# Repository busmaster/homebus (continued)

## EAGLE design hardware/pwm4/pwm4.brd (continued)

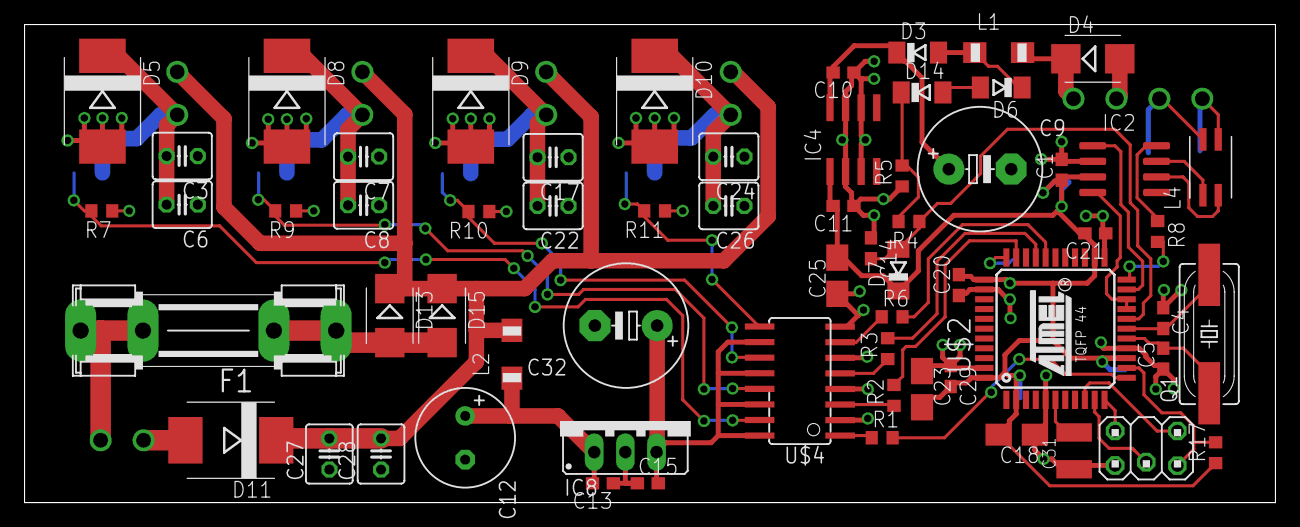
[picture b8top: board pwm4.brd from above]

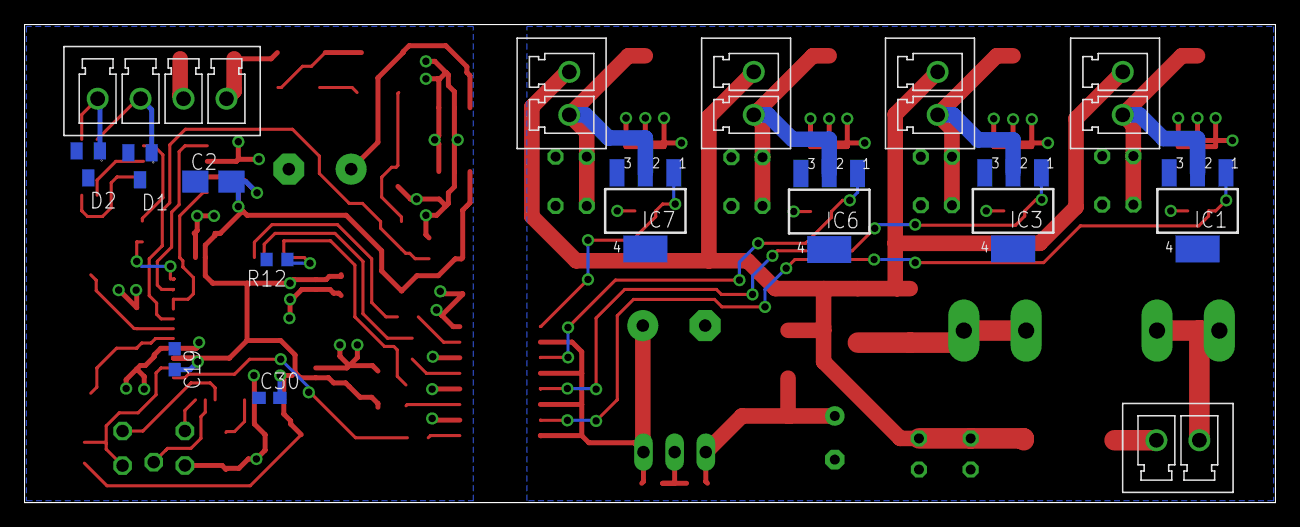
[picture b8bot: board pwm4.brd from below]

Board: 2 copper layers, 102.0 x 39.0 mm, 79 parts (16 on the bottom side), 46 nets.

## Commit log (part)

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2015-11-28 status led integration
2015-11-29 allow client pty while sio device is not yet available
2015-12-01 mega88 clock calibration
2015-12-05 correction of build directory path
2016-01-25 new bus telegram types for clock calibration
2016-01-25 clock calibration
2016-01-25 clock calibraton firmware for atmega88 based devices
2016-02-01 sio send lockup
2016-02-01 change of manufacturer and product string
2016-02-09 sio driver reports one received character on startup
2016-02-09 file mode changes
2016-02-11 Update README
    Test2
2016-02-19 elko position move
2016-02-23 bootloader for rs485if
2016-02-25 Fix usage message in eventmonitor and monitor
2016-02-29 firmwareupdate doesn't start due to buffered rx frames in sio device
2016-02-29 adapt file mode
2016-02-29 remove debug sio support
2016-02-29 prepare usage of siosingle
2016-03-08 removed bit offset undefs for m128 (moved to sio_c.h)
2016-03-08 version 1.05 (use of siosingle)
2016-03-08 use of siosingle for switchv2
2016-03-08 preparation for siosingle usage at do31 and rs485if
2016-03-13 board specific modules for rs485if
2016-03-15 atmega1284 adaptions
2016-03-19 dmx test
2016-03-19 correction of BUS_TRANSCEIVER_POWER_UP macro
2016-03-19 part value actualization
2016-03-19 set unix line termination
2016-03-20 port settings
2016-04-10 doc for initial flash setup
2016-04-10 correction of programming steps
2016-05-09 change actval from max wind to current wind
2016-05-16 auto switch off for lamp in garage and bathroom
2016-05-30 read command from stdin to terminate process
2016-05-30 correction of select rfds setup
2016-06-27 New window for kitchen. Support addition kitchen lamp.
2016-06-27 new window for kitchen
2016-09-18 change of socket_1 relais connection from NO to NC
2016-09-18 add support for 14.7456MHz and 1.8432MHz clock
2016-09-18 hardware design pwm4
2016-09-19 new command: generate a switch event
2016-09-21 set default own address in server mode
2016-09-21 set default own address in server mode to command line parameter
2016-09-21 converted to unix line termination
2016-09-21 setup window for disabling the doorbell
2016-10-01 changed crystal frequency
2016-10-01 add support for rs485if and pwm4 devices
2016-10-03 initial version of pwm4 application
2016-10-03 missing file
2016-10-03 rs485 test
2016-10-03 support for rs485f and pwm4
2016-10-10 reduce flash usage by sio tx simplification
2016-10-15 support rs485if and pwm4 actval
2016-10-15 optocoupler input and output resistor change
2016-10-17 output restore on power on
2016-10-17 unix line termination
2016-10-17 pwm for switch 46
2016-10-25 new command inforange for bus scan
2016-10-30 enable pullup on all input pins
2016-12-14 missing header
2017-01-03 save max wind value to eeprom
2017-01-03 rearrangement of buttons
2017-01-03 file mode
2017-01-04 sleep before flushing the sio input on startup
2017-01-17 use siosingle
2017-01-31 pwm4: set pwm frequency to 900 Hz from 225 Hz
    This high frequency is required due to instability of the used power supply
    (Meanwell LRS-50-24).
2017-01-31 pwm4 sio: support for additional cpu clocks
2017-02-18 eventmonitor: support device type PWM4
2017-02-27 removed debug print
2017-02-28 pwm: extension of interface: separate function for on/off
2017-02-28 sio: support EVEN parity
2017-02-28 pwm4 application: use extended pwm interface
2017-02-28 smartmeter tool: use EVEN parity
2017-02-28 new hardware: smartmeter interface
2017-03-14 smartmeterif: initial debug version
2017-03-18 smartmeter support
2017-03-18 pwm4: renaming mask -> set
2017-03-19 add new telegram type for diag data
2017-03-19 monitor: add support for diag telegram
2017-04-04 pwm4 application: delayed switch off of the common power supply
2017-04-04 smartmeterif hardware: value changes
2017-05-07 change \r\n to \n
2017-05-07 fflush stdout
2017-05-09 visu: reduce code duplication
2017-05-13 modulservice: check receiver address
2017-05-24 tools: mqtt: initial demo version
2017-06-04 mqtt: test
2017-06-04 tools: mqtt: pasre command line params
2017-06-05 tools: eventmonitor: optional listen only mode
2017-06-05 tools: mqtt: parameter for event listen address
2017-06-05 do31: eBusDevReqSetClientAddr does not work
2017-06-19 pwm4: unable to switch on after power fail
2017-06-20 tools: mqtt: subscriber support for do31 shader
2017-07-02 tools: mqtt: command line parameter for broker address/port
2017-07-02 tools: mqtt: debian init script example
2017-07-11 tools: mqtt: wait for response on DO31 ReqSetValue
2017-07-11 usbif: use siosingle
2017-07-15 tools: bottongpio: initial version
2017-07-15 tools: buttongpio: wrong telegram processing
2017-07-16 tool: mqtt: extend example configuration
2017-07-22 tools: mqtt: add lights stairs
2017-07-25 tools: modulservice: support changed pwm4 actval protocol
2017-07-25 pwm4: wrong actval state
2017-07-29 tools: mqtt: add PWM4 support
2017-08-09 tools: mqtt: sw8 device support
2017-10-17 buttongpio: trigger on swtichstate additionally
2017-10-31 switchv2a: replace switchState by actualValue telegrams
2017-10-31 project241: use eDigOut30 for door light
2017-11-07 bus: introduction gettime/settime telegram types
2017-11-11 application240: door light auto/on/off
2017-11-11 mqtt: topic extension
2017-11-12 buttongpio: add supoort for eBusDevReqActualValueEvent/sw8 telegram
2017-11-20 visu: implement ButtonBackPressed to call dialog's hide methode
2017-11-20 visu: support mjpeg camera
2017-11-26 visu: auto mode for door light
2017-11-27 visu: remove moduleservice debug prints
2017-11-28 visu: smartmeter support
2017-12-05 added .gitignore
2017-12-05 visu: do not smartmeter from startup
2017-12-11 add missing files
2017-12-11 add hardware
2018-02-24 monitor: support eBusDevTypeSmIf
2018-02-24 change to unix line ending
2018-02-25 switchv2_garage: optimize for size
2018-02-25 switchv2_luminance: optimize for size
2018-02-25 monitor: add setvar/getvar support
2018-02-25 monitor: output format cleanup
2018-04-03 bus: busvar support
2018-04-03 monitor: use variable for compiler options
2018-04-03 monitor: add setvar/getvar result code
2018-04-07 busvar: change index type to uint8_t from uint16_t
2018-04-08 monitor: wrong usage help for option logfile
2018-05-12 busvar: stabilisation
2018-06-26 busvar: make variable value peristent to eeprom optionally
2018-06-26 klaus240: use siosingle
2018-07-28 tools: initial varserver
2018-09-22 bustest: correction of library dependency order
2018-10-08 bus: pwm16 protocol support
2019-01-19 sonoff_socket: initial version
2019-10-30 sw88 1.06 hAT
2019-10-30 Anpassungen
2019-10-30 gitignore
2019-10-30 Hardwarelayouts
2019-10-30 Bootloader
2019-10-30 pwm16
2019-10-30 Projekt hinzugefügt
2019-10-30 missing makefile
2019-10-30 Eagle Files pwm16 added
2019-11-01 Portserver für Webapp
2019-11-07 spelling error
2019-11-08 tasttimeout
2019-11-25 do31: set reset state of interrupt mask registers
    The bootloader might leave interrupt mask register settings that
    can trigger unexcepted interrupts. These unexpected interrupt are
    handled by the default handler that calls the reset handler.
2020-05-03 mqtt: support sw8 input actval event
    On publishing mqtt sw8 input events a bus actval event is generated:
    mosq_publish ... -t home/eingang/bewegungsmelder/set -m 1
    -> bus actval event to all receivers from the configuration receiver option
    -> mqtt publish home/eingang/bewegungsmelder/actual
    The configuration has to be extended by the receiver option, e.g.:
    - topic: home/eingang/bewegungsmelder
2020-05-24 busvar: whitespace cleanup
2020-05-29 mqtt: add bus variable support
    bus device sends ReqSetVar to mqtt -> publish variable actual value
    publish variable set value to mqtt -> ReqSetVar to bus device
    To enable subscribtion to bus variables the bus device has to send ReqSetVar
    to mqtt virtual bus device.
2020-05-31 monitor: fix line feed output of RespSetVar
2020-05-31 visu: use new creator
2020-06-09 mqtt: publish var directly on var subscription callback
    Before publish var was triggered by bus ReqSetVar only.
2020-06-11 mqtt: do not publish retained
2020-06-11 mqtt: undo disable retained messages
2020-06-14 mqtt: support DO31 active low outputs
2020-06-14 mqtt: rename variable topic in example config
2020-06-19 visu: replace the proprietary device access with mqtt
2020-06-21 visu: remove unused variable
2020-06-23 klaus240: use bus variables for bell mode and door light mode
2020-07-03 bus: extend ActualValueEvent by smif
2020-07-03 smif: add ActualValueEvent for smartmeter data
    The ActualValueEvent is enabled by setting bus variable 0 to 1.
    After N seconds bus variable 0 is reset automatically. N is read from
    bus variable 1. The receiver address of the ActualValueEvent is read from
    bus varibale 2.
2020-07-04 smif: fix message type for ActualValueEvent
2020-07-04 monitor: add supoort for smif ActualValueEvent
2020-07-04 visu: support smartmeter
2020-07-09 bus: save firmware from device to file
2020-07-09 tools: add firmwaresave
2020-07-09 monitor: support firmware save protocol extension
2020-07-10 smif: support reading of firmware flash image
2020-07-11 smif: force a ActualValueEvent on enabling it
2020-07-11 pwm4: support reading of firmware flash image
2020-07-14 firmwaresave: fix compiler warning
2020-07-17 mqtt: do not call BusCheck multiple times in main loop
    When BusCheck is called it consumes the last packet from the receive queue.
    So serve_bus was disabled to get all packet from bus and some publish messages
    were missing sporadically.
2020-07-21 bus: change file attributes
2020-07-23 mqtt: publish actual value of bbusvar on bus response
2020-07-23 visu: use QHash to match compare strings
2020-07-25 visu: auto reconnect to mqtt broker
2020-07-26 sonoff_socket: remove startup mqtt message
2020-08-06 visu: adapt to 800x480 resolution
2020-08-06 visu: generalize device support
    hwmon devices are searched by name.
2021-05-15 mqtt: disable logging of stdout to syslog
2021-07-10 Add keyboard device
2021-07-28 hardware: smartmeterif: Add png
2021-08-23 Integrate support for ABUS CFA3100
    CFA3100 is controlled by CFF3100 bluetooth remote control. Bus access to CFF3100 is implemented by
    cff3100if device. For user code input a keypad is used.
    Use case:
    1) User enters code at the keypad
    2) The keypad bus device, based on switchv2 hardware, sends the key codes entered to the
    cff3100if device
2021-08-28 cff3100if: Read lock state
2021-08-28 hardware: cff3100if: Beautify schematic
2021-08-29 cff3100if: Add setvalue
2021-08-30 cff3100if: Fix key code handling
2021-09-25 tools: mqtt: Support keyrc
2021-10-25 cff3100if: Send response at end of state sequence
    The bus response was sent but while the lock state machine was in
    termination state, no further requests were accepted.
2021-11-28 stoveguard: initial fw version
2021-12-08 stoveguard: Add initial hardware revision
2022-03-25 visu: Change to chunked mjpg transfer encoding
    Required due to camera update to Debian 11.
2022-05-01 keyrc: Add key code for eBusButtonPressedX telegram
2022-05-01 klaus240: Add function for switching 'Licht Eingang' manually
2022-07-09 hardware/smartmeterif: Board version 2
    - voltage regulator housing collision
    - size reduction
2022-07-30 visu: Add smartmeter data
2023-04-16 visu: Add PV data
2023-04-17 visu: Show current power
2023-08-27 visu: Remove P+ and P-
2023-09-17 visu: Separate meter/pv, doorlocker and io events
    doorlocker state shall not be updated by meter/pv or io events.
2023-12-15 stoveguard: Send output event to clients
2023-12-15 monitor: Add support for stoveguard
2024-05-02 hardware: Add usbif schematics png
2026-01-02 visu: Fix mjpeg processing
    A completed jpeg image might be contained in a single http chunk.
2026-01-06 Tools: portserver: Add systemd install example
2026-01-18 DO31 sio: undef U2X
    Wrong UART baud rate at mega128@1MHz. Double baud rate not working.
2026-01-18 DO31 bootloader: Add readme for device setup
2026-01-18 DO31 bootloader: Remove AVRStudio project file
2026-01-18 DO31 bootloader: Add bootloader for devices using 1MHz MCU clock
2026-01-18 makefile: avr-size: Remove unsupport option -C
    Newer versions don't support -C anymore.
2026-01-25 Add projects DO31 Kurt
2026-03-08 Tools: mqtt: Fix typo
2026-04-27 visu: Display storage data
2026-05-01 visu: Adapt smartmeter window geometry
2026-06-21 Ordered PCB
